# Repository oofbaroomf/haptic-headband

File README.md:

### Haptic Navigation Headband

Hello, I am Amitav. I'm making this project with Aarush (graphic designer) and Toby, who's doing the coding. This project is a headband for blind people that uses two distance sensors and three vibration motors to give feedback about nearby obstacles.

A relative of mine lost his sight through optic nerve atrophy, which got me started on this. He's our client, and we want to find out whether the vibrations are useful and the band is comfortable. The idea is extra feedback without covering his ears.

### The idea

A HUZZAH32 reads the distance sensors and controls the motors. A BNO085 measures orientation, and we're keeping Wi-Fi and Bluetooth in the plan.

We're reusing an old helmet band, with Velcro for the lighter parts and a printed housing for the PCB. The battery has a seperate holder. Trying to keep it simple to put together and not too bulky.

### Progress so far

The PCB and CAD files are here. JLCPCB reviewed the files, but the PCB order is still unpaid. We already have the HUZZAH32, sensors, BNO085, motors, switch and USB-C charger.

We haven't tested the complete device yet, and Toby's firmware isn't in the repo yet. We'll need to test for heat once the parts arrive.

Once this one works, hopefuly we can make a smaller, lighter and cheaper version.

### Drawings

These are Aarush's early sketches. Some details changed along the way.

Exploded CAD diagram :)

### PCB

The PCB connects everything, with motor drivers and external Pololu power modules.

### Files

KiCad: https://github.com/oofbaroomf/haptic-headband/tree/main/pcb

Gerbers: https://github.com/oofbaroomf/haptic-headband/blob/main/gerbers/Haptic_Headband_R3A_JLCPCB_EXPERIMENTAL_PROTOTYPE.zip

Assembly files: https://github.com/oofbaroomf/haptic-headband/tree/main/pcb/assembly

STEP: https://github.com/oofbaroomf/haptic-headband/blob/main/cad/Headband_Assembly.step

Fusion and print files: https://github.com/oofbaroomf/haptic-headband/tree/main/cad

Journal: https://github.com/oofbaroomf/haptic-headband/blob/main/JOURNAL.md

### Putting it together

Plan is to check the assembled PCB and regulator settings, test the modules on the bench, then fit everything to the printed parts and band. A proper build and flashing guide will follow once we've tried it.

### Parts

Our parts list, so we can keep track of everything while we build. We're still working out how much strap material and which mounting hardware we need.

CSV BOM: https://github.com/oofbaroomf/haptic-headband/blob/main/BOM.csv

| Part | Quantity | Reference | Link |
| --- | ---: | --- | --- |
| 4172 | 1 | U1 | https://github.com/adafruit/Adafruit-ESP32-HUZZAH-Breakout-PCB |
| DMN2056U-7 | 4 | Q1 Q2 Q3 Q5 | https://jlcpcb.com/partdetail/C332302 |
| DMP2035U-7 | 2 | Q4 Q6 | https://jlcpcb.com/partdetail/C110499 |
| 1N5819 | 3 | D1 D2 D3 | https://jlcpcb.com/partdetail/C110032 |
| MFR-25FTF52-330R | 3 | R1 R2 R3 | https://jlcpcb.com/partdetail/C1372966 |
| MFR-25FBF52-1K | 3 | R4 R5 R6 | https://jlcpcb.com/partdetail/C1364484 |
| MFR-25FTE52-100K | 1 | R12 | https://jlcpcb.com/partdetail/C172965 |
| MFR-25FTE52-10K | 4 | R10 R11 R13 R14 | https://jlcpcb.com/partdetail/C172967 |
| EEUFR1A221 | 1 | C1 | https://jlcpcb.com/partdetail/C407869 |
| EEUFM1E101 | 1 | C2 | https://jlcpcb.com/partdetail/C713389 |
| EEUFM1E101 | 1 | C3 | https://jlcpcb.com/partdetail/C713389 |
| EEUFR1A221 | 1 | C10 | https://jlcpcb.com/partdetail/C407869 |
| 805 / SS-12E17G2 | 1 | SW1 | https://cdn-shop.adafruit.com/product-files/805/SS-12E17G2-revised.pdf |
| B2B-XH-A(LF)(SN) | 3 | J1 J2 J3 | https://jlcpcb.com/partdetail/C158012 |
| B6B-XH-A(LF)(SN) | 2 | J4 J5 | https://jlcpcb.com/partdetail/C144397 |
| B6B-PH-K-S(LF)(SN) | 1 | J6 | https://jlcpcb.com/partdetail/C131342 |
| B2B-PH-K-S(LF)(SN) | 1 | J7 | https://jlcpcb.com/partdetail/C131337 |
| B3B-PH-K-S(LF)(SN) | 1 | J8 | https://jlcpcb.com/partdetail/C131339 |
| B4B-PH-K-S(LF)(SN) | 1 | J9 | https://jlcpcb.com/partdetail/C131334 |
| B5B-PH-K-S(LF)(SN) | 1 | J10 | https://jlcpcb.com/partdetail/C157993 |
| TSW-102-07-G-S | 1 | JP1 | https://jlcpcb.com/partdetail/C7402729 |
| TCA9517DR | 1 | U2 | https://jlcpcb.com/partdetail/C182421 |
| SN74CBTLV1G125DBVR | 1 | U6 | https://jlcpcb.com/partdetail/C2653264 |
| SN74LVC2G07DBVR | 1 | U3 | https://jlcpcb.com/partdetail/C37708 |
| SN74LVC1G125DBVR | 2 | U4 U5 | https://jlcpcb.com/partdetail/C23654 |
| RC1206FR-074K7L | 2 | R15 R16 | https://jlcpcb.com/partdetail/C137262 |
| RC1206FR-0710KL | 4 | R17 R18 R21 R22 | https://jlcpcb.com/partdetail/C132649 |
| RC1206FR-07100KL | 2 | R19 R20 | https://jlcpcb.com/partdetail/C137393 |
| C1206C104K5RACTU | 6 | C4 C5 C6 C7 C8 C9 | https://jlcpcb.com/partdetail/C41430990 |
| 0251002.NRT1L | 1 | F1 | https://jlcpcb.com/partdetail/C151088 |
| PHR-3 | 1 | MATE_PH3 | https://www.jst.com/wp-content/uploads/2021/08/ePH-new.pdf |
| PHR-4 | 1 | MATE_PH4 | https://www.jst.com/wp-content/uploads/2021/08/ePH-new.pdf |
| PHR-5 | 1 | MATE_PH5 | https://www.jst.com/wp-content/uploads/2021/08/ePH-new.pdf |
| PHR-6 | 1 | MATE_PH6 | https://www.jst.com/wp-content/uploads/2021/08/ePH-new.pdf |
| XHP-2 | 3 | MATE_XH2 | https://www.jst.com/wp-content/uploads/2025/06/eXH.pdf |
| XHP-6 | 2 | MATE_XH6 | https://www.jst.com/wp-content/uploads/2025/06/eXH.pdf |
| ASPHSPH24K305 | 10 | CONTACT_PH | https://www.digikey.co.uk/en/products/detail/jst-sales-america-inc/ASPHSPH24K305/6009459 |
| ASXHSXH22K305 | 10 | CONTACT_XH | https://www.digikey.co.uk/en/products/detail/jst-sales-america-inc/ASXHSXH22K305/6684932 |
| SSW-115-01-T-S | 2 | SK1 SK2 | https://jlcpcb.com/partdetail/C6686518 |
| PIM622 | 2 | TOF_LEFT TOF_RIGHT | https://cdn.shopify.com/s/files/1/0174/1800/files/VL53L5CX-schematic.pdf?v=1654004213 |
| 4754 (selected; confirm purchased SKU) | 1 | IMU1 | https://learn.adafruit.com/adafruit-9-dof-orientation-imu-fusion-breakout-bno085/pinouts |
| S7V8F3 / 2122 | 1 | REG_SENS | https://www.pololu.com/product/2122 |
| S7V8A / 2118 | 1 | REG_MOTOR | https://www.pololu.com/product/2118 |
| Reference only: 10B27.3018 / Adafruit1201 | 3 | M_LEFT M_RIGHT M_FRONT | https://thepihut.com/products/vibrating-mini-motor-disc |
| ICR18650 4400mAh 3.7V | 1 | BAT1 | https://shop.pimoroni.com/products/lithium-ion-battery-pack?variant=23417820423 |
| S7V8A / 2118 | 1 | REG_CTRL | https://www.pololu.com/product/2118 |
| 4410 | 1 | CHARGER1 | https://www.adafruit.com/product/4410 |
| M7566-05 | 1 | JP1_SHUNT | https://www.harwin.com/products/M7566-05 |
| HB-VIN-JUMPER-01 (assembly drawing, not vendor MPN) | 1 | HARNESS_CTRL | Custom wire/link |

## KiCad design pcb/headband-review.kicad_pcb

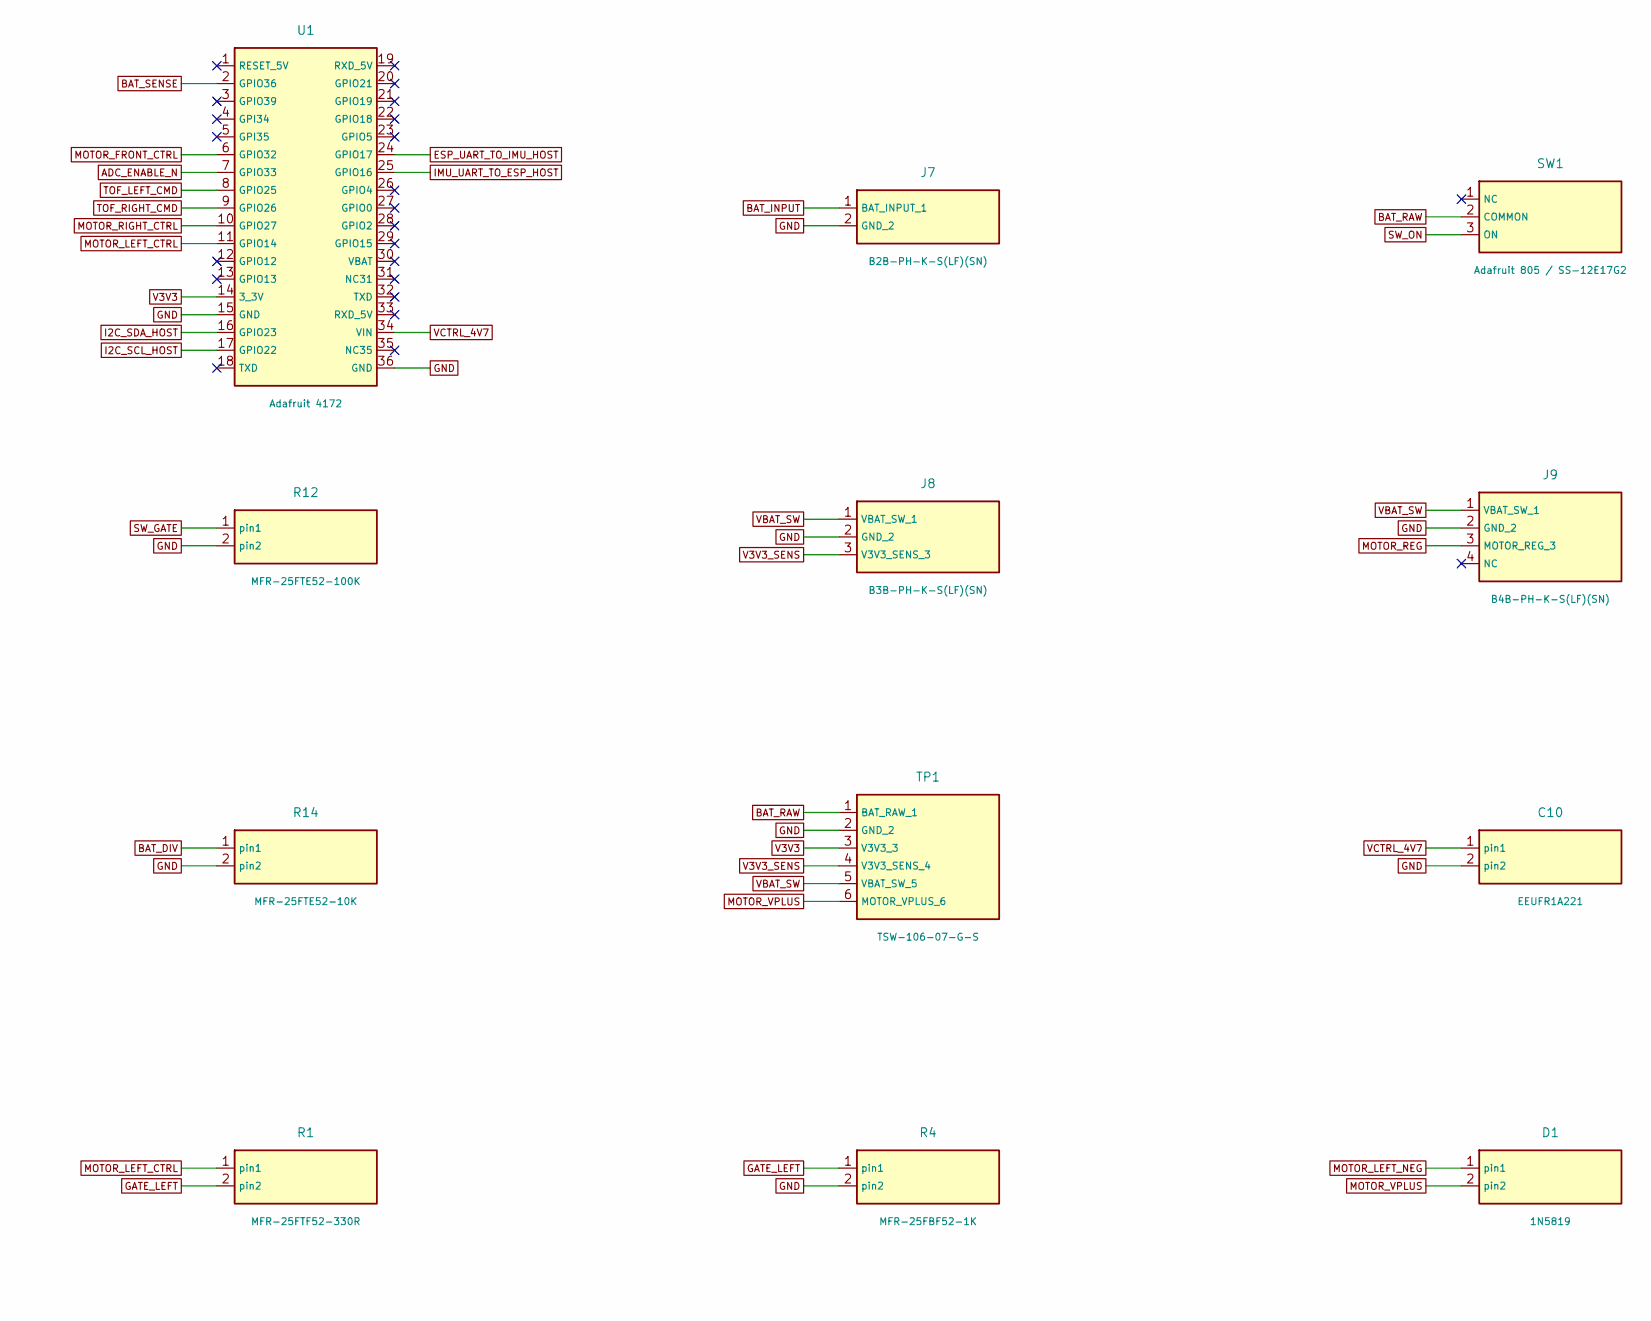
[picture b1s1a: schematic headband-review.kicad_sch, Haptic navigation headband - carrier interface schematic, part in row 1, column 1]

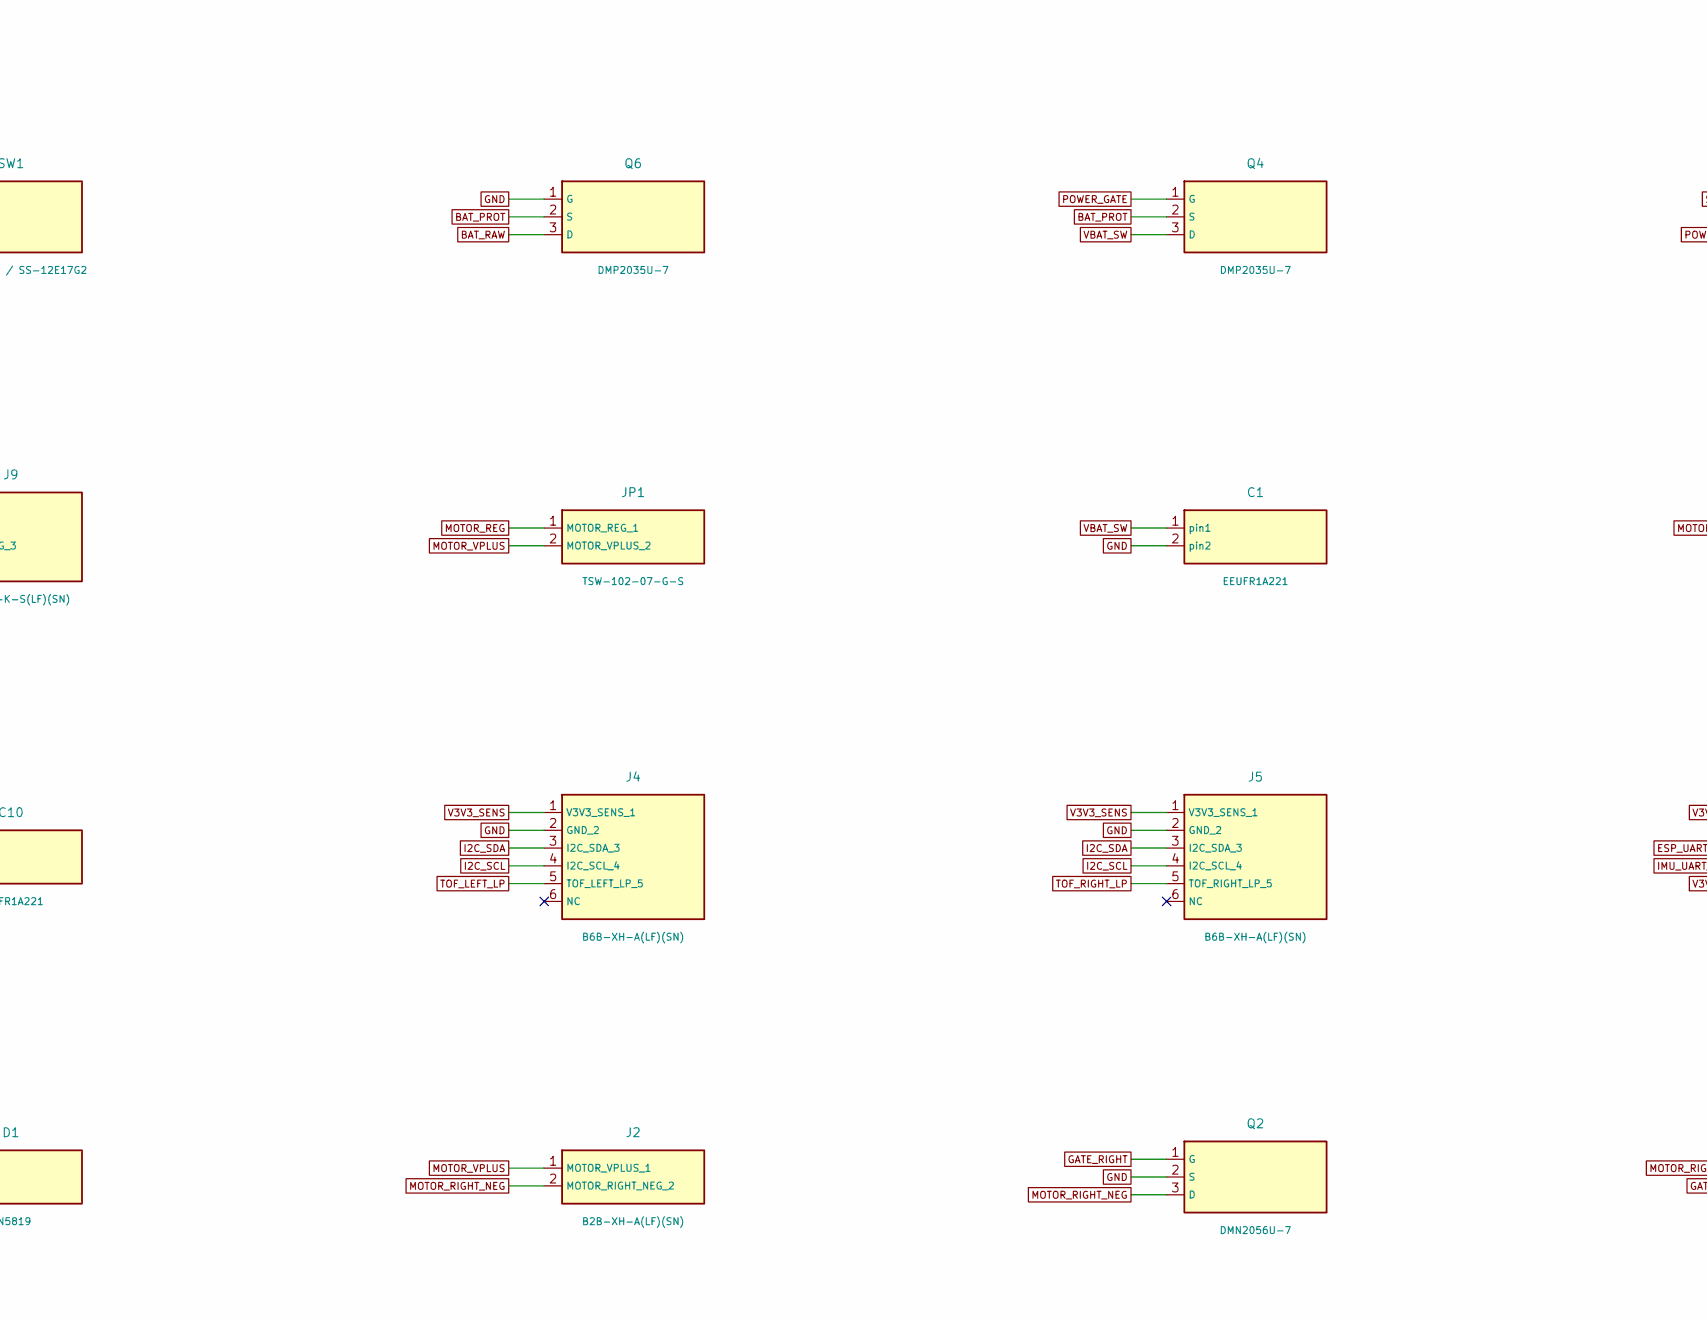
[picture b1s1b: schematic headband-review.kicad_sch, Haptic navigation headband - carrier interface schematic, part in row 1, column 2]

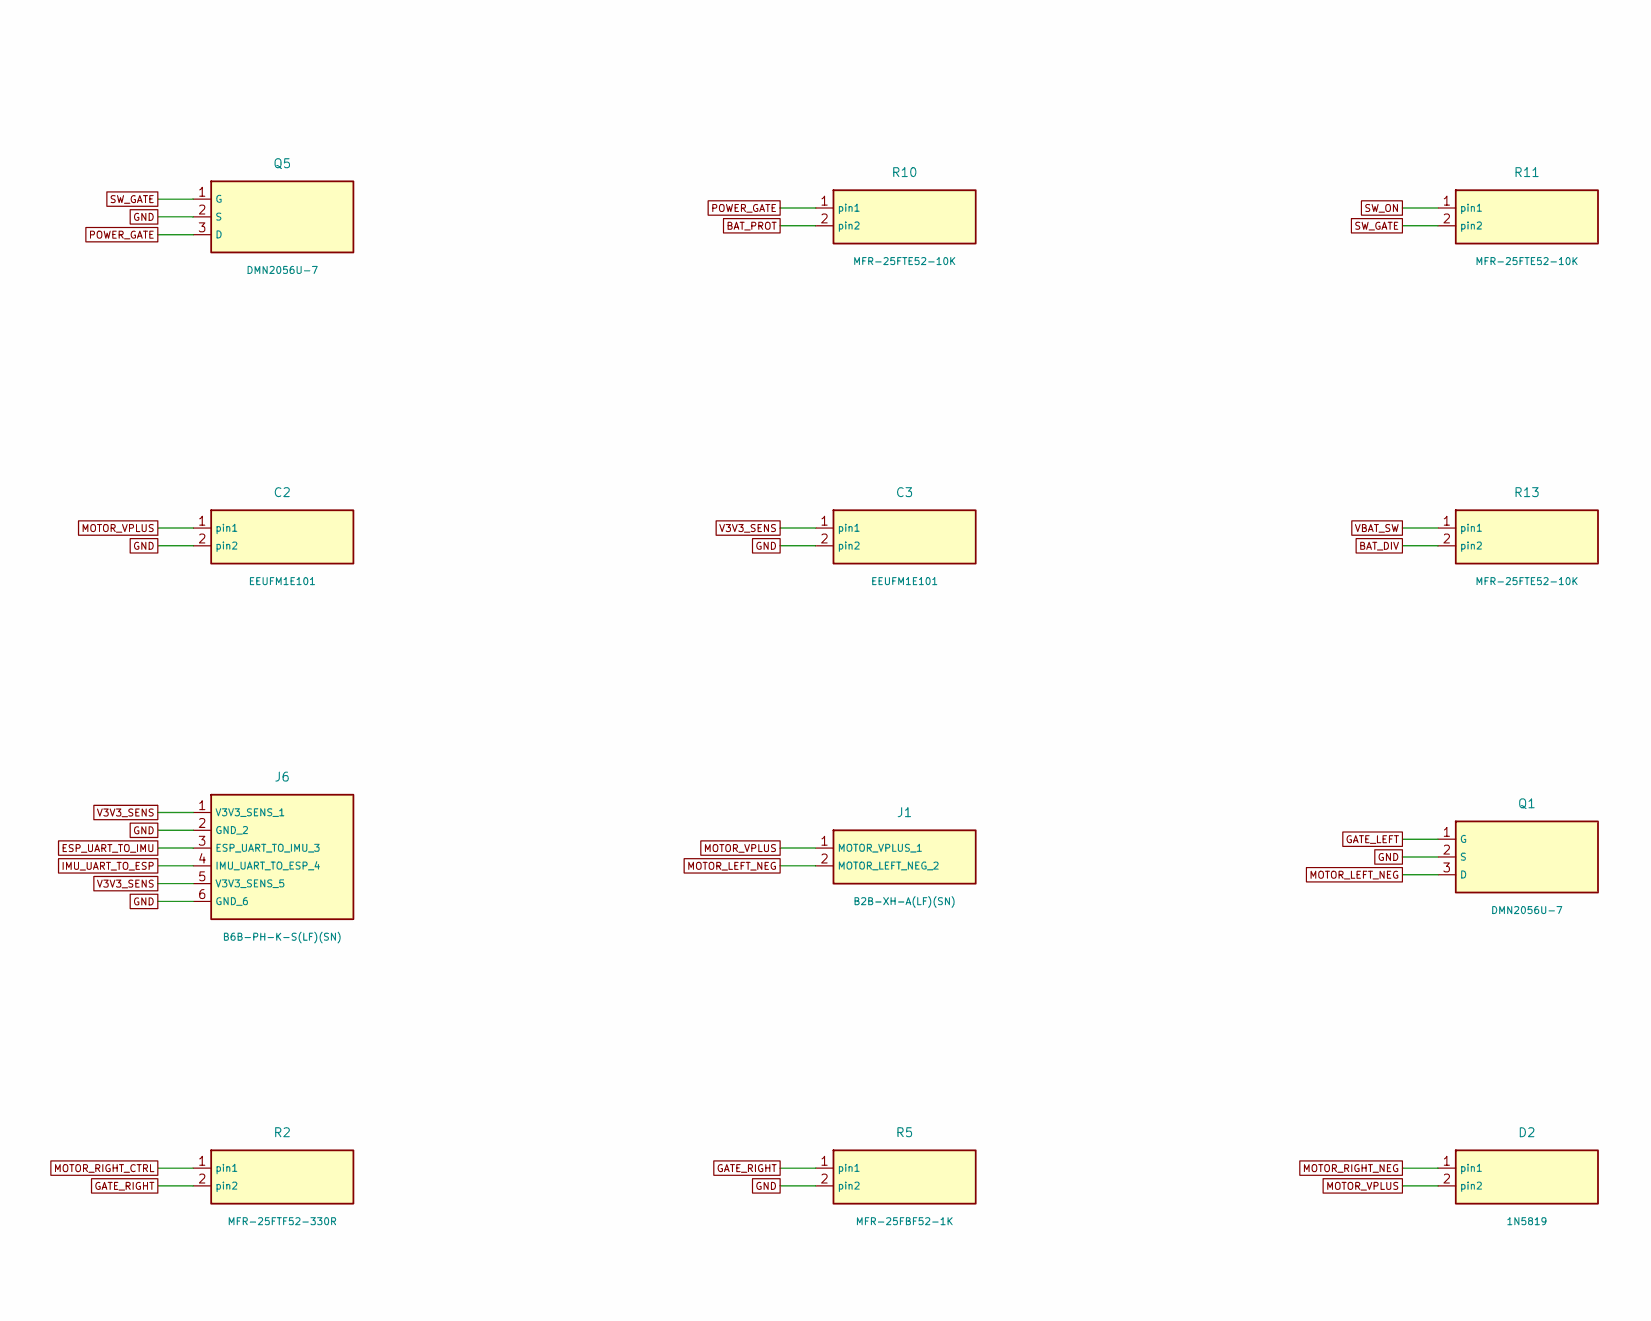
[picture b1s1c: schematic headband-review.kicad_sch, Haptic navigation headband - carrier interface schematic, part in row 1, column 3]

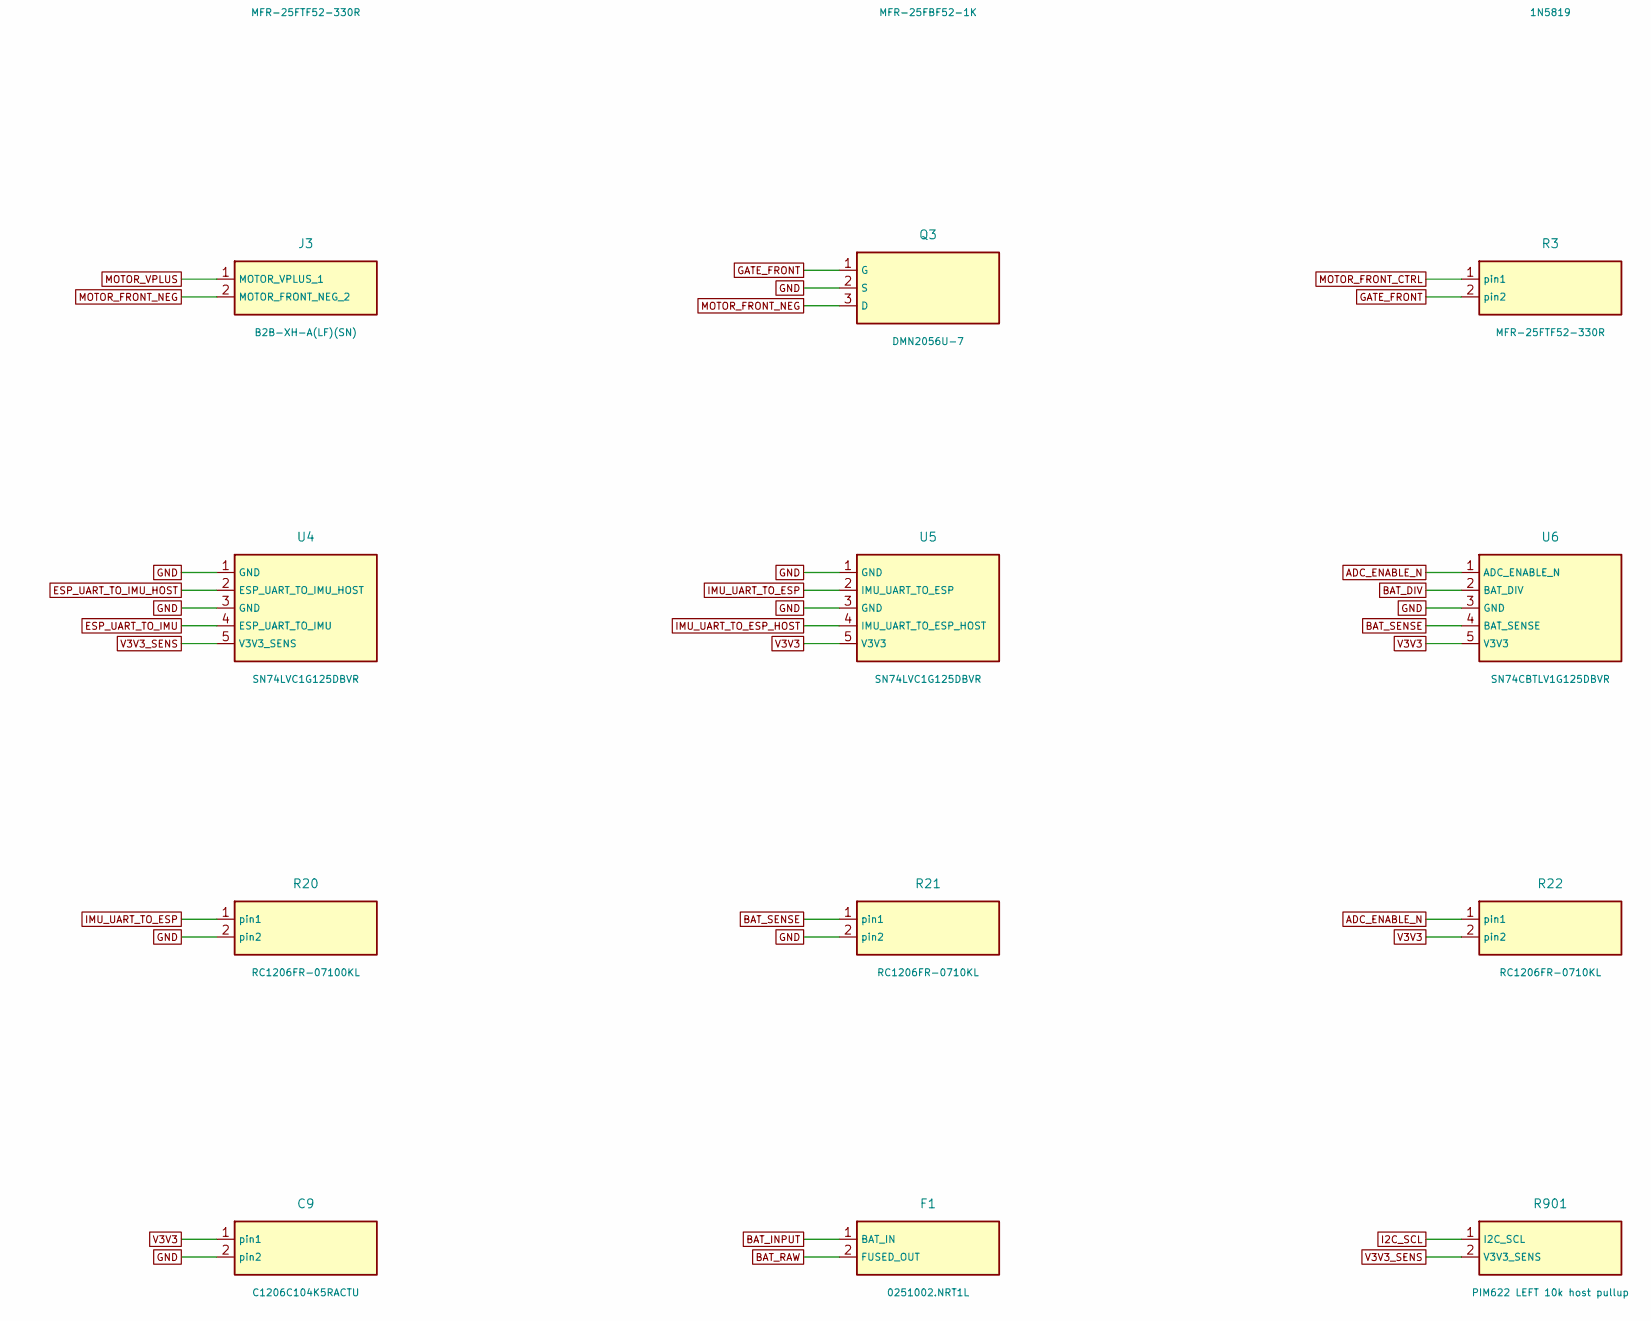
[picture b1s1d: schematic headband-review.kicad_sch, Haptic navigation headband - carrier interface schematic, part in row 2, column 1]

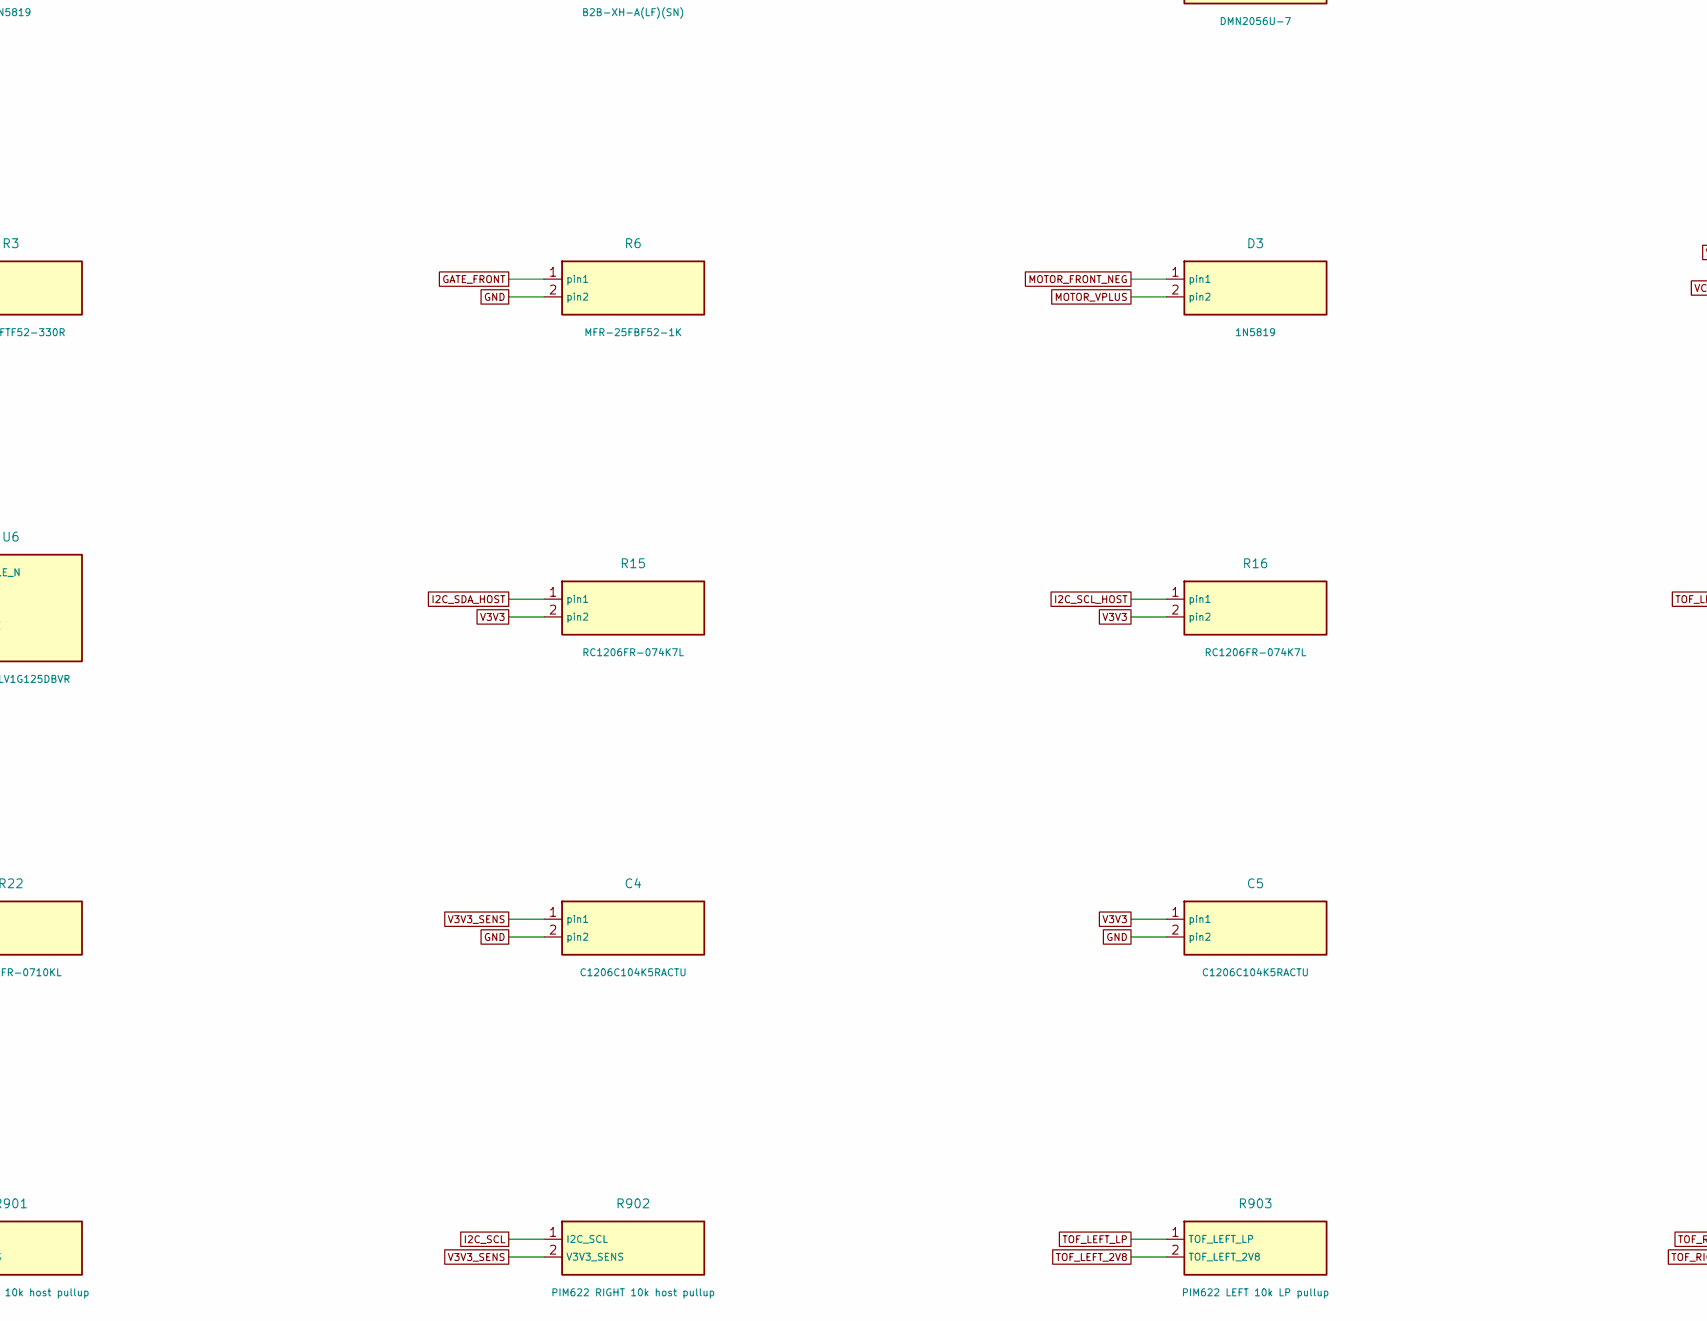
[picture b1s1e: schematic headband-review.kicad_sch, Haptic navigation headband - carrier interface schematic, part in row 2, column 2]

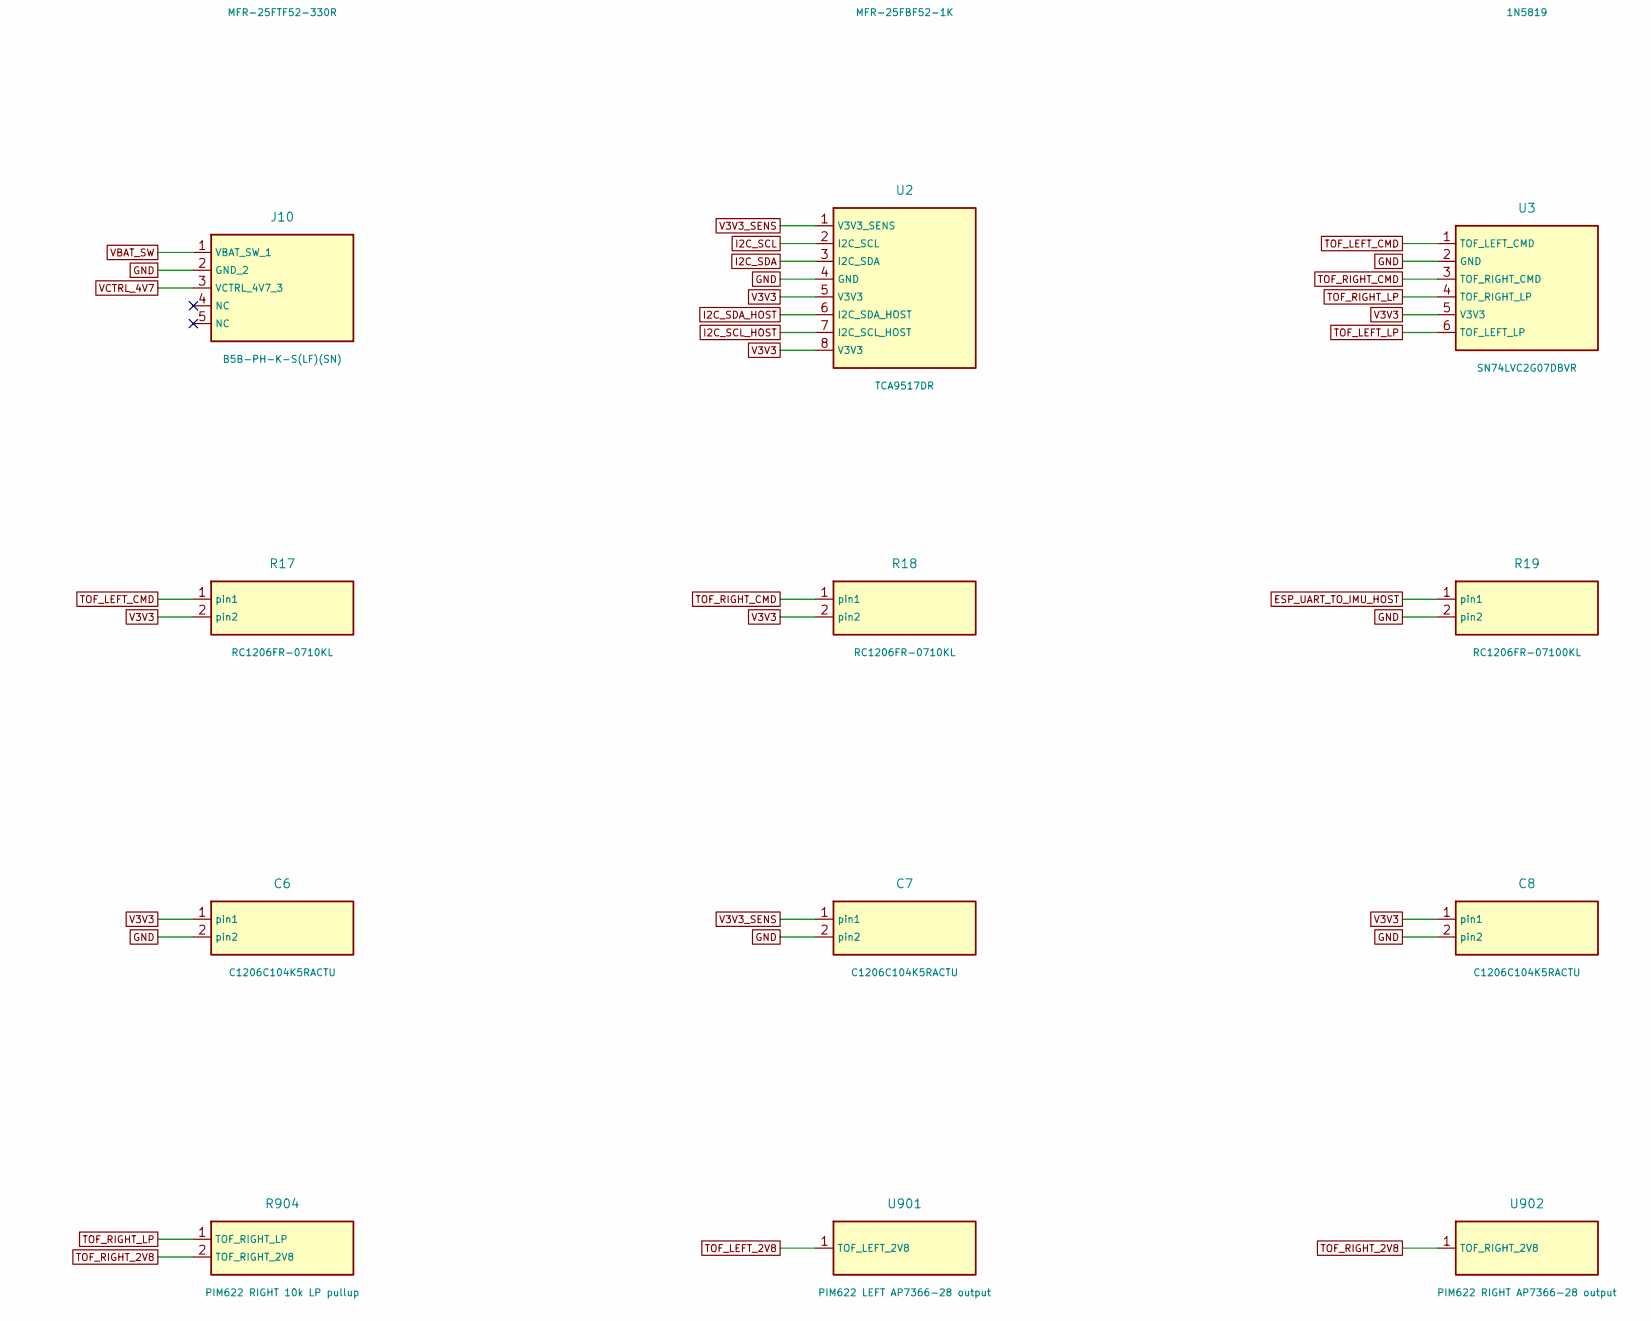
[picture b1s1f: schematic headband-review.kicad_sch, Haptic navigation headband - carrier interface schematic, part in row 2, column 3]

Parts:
C1: EEUFR1A221; HB_C1
C2: EEUFM1E101; HB_C2
C3: EEUFM1E101; HB_C3
C4: C1206C104K5RACTU; HB_C4
C5: C1206C104K5RACTU; HB_C5
C6: C1206C104K5RACTU; HB_C6
C7: C1206C104K5RACTU; HB_C7
C8: C1206C104K5RACTU; HB_C8
C9: C1206C104K5RACTU; HB_C9
C10: EEUFR1A221; HB_C10
D1: 1N5819; HB_D1
D2: 1N5819; HB_D2
D3: 1N5819; HB_D3
F1: 0251002.NRT1L; HB_F1
J1: B2B-XH-A(LF)(SN); HB_J1
J2: B2B-XH-A(LF)(SN); HB_J2
J3: B2B-XH-A(LF)(SN); HB_J3
J4: B6B-XH-A(LF)(SN); HB_J4
J5: B6B-XH-A(LF)(SN); HB_J5
J6: B6B-PH-K-S(LF)(SN); HB_J6
J7: B2B-PH-K-S(LF)(SN); HB_J7
J8: B3B-PH-K-S(LF)(SN); HB_J8
J9: B4B-PH-K-S(LF)(SN); HB_J9
J10: B5B-PH-K-S(LF)(SN); HB_J10
JP1: TSW-102-07-G-S; HB_JP1
Q1: DMN2056U-7; HB_Q1
Q2: DMN2056U-7; HB_Q2
Q3: DMN2056U-7; HB_Q3
Q4: DMP2035U-7; HB_Q4
Q5: DMN2056U-7; HB_Q5
Q6: DMP2035U-7; HB_Q6
R1: MFR-25FTF52-330R; HB_R1
R2: MFR-25FTF52-330R; HB_R2
R3: MFR-25FTF52-330R; HB_R3
R4: MFR-25FBF52-1K; HB_R4
R5: MFR-25FBF52-1K; HB_R5
R6: MFR-25FBF52-1K; HB_R6
R10: MFR-25FTE52-10K; HB_R10
R11: MFR-25FTE52-10K; HB_R11
R12: MFR-25FTE52-100K; HB_R12
R13: MFR-25FTE52-10K; HB_R13
R14: MFR-25FTE52-10K; HB_R14
R15: RC1206FR-074K7L; HB_R15
R16: RC1206FR-074K7L; HB_R16
R17: RC1206FR-0710KL; HB_R17
R18: RC1206FR-0710KL; HB_R18
R19: RC1206FR-07100KL; HB_R19
R20: RC1206FR-07100KL; HB_R20
R21: RC1206FR-0710KL; HB_R21
R22: RC1206FR-0710KL; HB_R22
R901: PIM622 LEFT 10k host pullup
R902: PIM622 RIGHT 10k host pullup
R903: PIM622 LEFT 10k LP pullup
R904: PIM622 RIGHT 10k LP pullup
SW1: Adafruit 805 / SS-12E17G2; HB_SW1
TP1: TSW-106-07-G-S; HB_TP1
U1: Adafruit 4172; HB_U1
U2: TCA9517DR; HB_U2
U3: SN74LVC2G07DBVR; HB_U3
U4: SN74LVC1G125DBVR; HB_U4
U5: SN74LVC1G125DBVR; HB_U5
U6: SN74CBTLV1G125DBVR; HB_U6
U901: PIM622 LEFT AP7366-28 output
U902: PIM622 RIGHT AP7366-28 output

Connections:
ADC_ENABLE_N: R22.1, U1.7 (GPIO33), U6.1 (ADC_ENABLE_N)
BAT_DIV: R13.2, R14.1, U6.2 (BAT_DIV)
BAT_INPUT: F1.1 (BAT_IN), J7.1 (BAT_INPUT_1)
BAT_PROT: Q4.2 (S), Q6.2 (S), R10.2
BAT_RAW: F1.2 (FUSED_OUT), Q6.3 (D), SW1.2 (COMMON), TP1.1 (BAT_RAW_1)
BAT_SENSE: R21.1, U1.2 (GPIO36), U6.4 (BAT_SENSE)
ESP_UART_TO_IMU: J6.3 (ESP_UART_TO_IMU_3), U4.4 (ESP_UART_TO_IMU)
ESP_UART_TO_IMU_HOST: R19.1, U1.24 (GPIO17), U4.2 (ESP_UART_TO_IMU_HOST)
GATE_FRONT: Q3.1 (G), R3.2, R6.1
GATE_LEFT: Q1.1 (G), R1.2, R4.1
GATE_RIGHT: Q2.1 (G), R2.2, R5.1
GND: C1.2, C2.2, C3.2, C4.2, C5.2, C6.2, C7.2, C8.2, C9.2, C10.2, J4.2 (GND_2), J5.2 (GND_2), J6.2 (GND_2), J6.6 (GND_6), J7.2 (GND_2), J8.2 (GND_2), J9.2 (GND_2), J10.2 (GND_2), Q1.2 (S), Q2.2 (S), Q3.2 (S), Q5.2 (S), Q6.1 (G), R4.2, R5.2, R6.2, R12.2, R14.2, R19.2, R20.2, R21.2, TP1.2 (GND_2), U1.15 (GND), U1.36 (GND), U2.4 (GND), U3.2 (GND), U4.1 (GND), U4.3 (GND), U5.1 (GND), U5.3 (GND), U6.3 (GND)
I2C_SCL: J4.4 (I2C_SCL_4), J5.4 (I2C_SCL_4), R901.1 (I2C_SCL), R902.1 (I2C_SCL), U2.2 (I2C_SCL)
I2C_SCL_HOST: R16.1, U1.17 (GPIO22), U2.7 (I2C_SCL_HOST)
I2C_SDA: J4.3 (I2C_SDA_3), J5.3 (I2C_SDA_3), U2.3 (I2C_SDA)
I2C_SDA_HOST: R15.1, U1.16 (GPIO23), U2.6 (I2C_SDA_HOST)
IMU_UART_TO_ESP: J6.4 (IMU_UART_TO_ESP_4), R20.1, U5.2 (IMU_UART_TO_ESP)
IMU_UART_TO_ESP_HOST: U1.25 (GPIO16), U5.4 (IMU_UART_TO_ESP_HOST)
MOTOR_FRONT_CTRL: R3.1, U1.6 (GPIO32)
MOTOR_FRONT_NEG: D3.1, J3.2 (MOTOR_FRONT_NEG_2), Q3.3 (D)
MOTOR_LEFT_CTRL: R1.1, U1.11 (GPIO14)
MOTOR_LEFT_NEG: D1.1, J1.2 (MOTOR_LEFT_NEG_2), Q1.3 (D)
MOTOR_REG: J9.3 (MOTOR_REG_3), JP1.1 (MOTOR_REG_1)
MOTOR_RIGHT_CTRL: R2.1, U1.10 (GPIO27)
MOTOR_RIGHT_NEG: D2.1, J2.2 (MOTOR_RIGHT_NEG_2), Q2.3 (D)
MOTOR_VPLUS: C2.1, D1.2, D2.2, D3.2, J1.1 (MOTOR_VPLUS_1), J2.1 (MOTOR_VPLUS_1), J3.1 (MOTOR_VPLUS_1), JP1.2 (MOTOR_VPLUS_2), TP1.6 (MOTOR_VPLUS_6)
unnamed: R903.2 (TOF_LEFT_2V8), U901.1
unnamed: R904.2 (TOF_RIGHT_2V8), U902.1
POWER_GATE: Q4.1 (G), Q5.3 (D), R10.1
SW_GATE: Q5.1 (G), R11.2, R12.1
SW_ON: R11.1, SW1.3 (ON)
TOF_LEFT_CMD: R17.1, U1.8 (GPIO25), U3.1 (TOF_LEFT_CMD)
TOF_LEFT_LP: J4.5 (TOF_LEFT_LP_5), R903.1 (TOF_LEFT_LP), U3.6 (TOF_LEFT_LP)
TOF_RIGHT_CMD: R18.1, U1.9 (GPIO26), U3.3 (TOF_RIGHT_CMD)
TOF_RIGHT_LP: J5.5 (TOF_RIGHT_LP_5), R904.1 (TOF_RIGHT_LP), U3.4 (TOF_RIGHT_LP)
V3V3: C5.1, C6.1, C8.1, C9.1, R15.2, R16.2, R17.2, R18.2, R22.2, TP1.3 (V3V3_3), U1.14 (3_3V), U2.5 (V3V3), U2.8 (V3V3), U3.5 (V3V3), U5.5 (V3V3), U6.5 (V3V3)
V3V3_SENS: C3.1, C4.1, C7.1, J4.1 (V3V3_SENS_1), J5.1 (V3V3_SENS_1), J6.1 (V3V3_SENS_1), J6.5 (V3V3_SENS_5), J8.3 (V3V3_SENS_3), R901.2 (V3V3_SENS), R902.2 (V3V3_SENS), TP1.4 (V3V3_SENS_4), U2.1 (V3V3_SENS), U4.5 (V3V3_SENS)
VBAT_SW: C1.1, J8.1 (VBAT_SW_1), J9.1 (VBAT_SW_1), J10.1 (VBAT_SW_1), Q4.3 (D), R13.1, TP1.5 (VBAT_SW_5)
VCTRL_4V7: C10.1, J10.3 (VCTRL_4V7_3), U1.34 (VIN)
